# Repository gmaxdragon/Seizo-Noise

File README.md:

# Seizo-Noise

> **Engineering update, 24 October 2026:** A separate [**Seizo Noise v2.1 native KiCad source**](v2_1/ENGINEERING_REVIEW.md) and matching [BOM](purchasing/BOM_HalfLife_v2_1.csv) have been added. The narrative and screenshots below document the original **v1 ESP32/12V board**, not the simplified v2.1 5V Pi audio carrier. The root BOM now shows the **v2.1 priced subset** ($34.46 before missing shipping, tax and hardware); the complete legacy v1 BOM is [archived](purchasing/legacy_v1_BOM_archive.csv). v2.1 CAD has archived clean ERC/DRC but is not approved for PCB fabrication or order until the actual jack and potentiometer fit is checked. Neither board has been physically assembled or audio-tested. This note is a technical engineering update and does not alter the owner's account of the project.

## Current Seizo Noise v2.1 BOM and pricing (October 24, 2026)

**Estimated listed parts and PCB subtotal: $34.46 USD across 17 lines.** Includes a **provisional $4.00 PCB fabrication allowance**. This is **not** a final shipped/project cost. Shipping, sales tax, enclosure, standoffs, adapter/power-supply and other unpriced assembly items are **not included**. Prices come from saved catalog checks and are **not a live checkout quote**.

| Part | Quantity | Unit price (USD) | Line total (USD) |
| --- | ---: | ---: | ---: |
| [J1: 2-pin 5.08mm screw terminal](https://www.digikey.com/en/products/detail/on-shore-technology-inc/OSTTC022162/614558) | 1 | $0.58 | $0.58 |
| [F1: 0.75A hold resettable PTC fuse](https://www.digikey.com/en/products/detail/littelfuse-inc/RXEF075/5015922) | 1 | $0.56 | $0.56 |
| [D1: Schottky 1A 40V axial diode DO41](https://www.digikey.com/en/products/detail/panjit-international-inc/1N5819-R2-00001/15806519) | 1 | $0.28 | $0.28 |
| [C1: 470uF 25V low ESR radial 10mm 5mm leads](https://www.digikey.com/en/products/detail/panasonic-electronic-components/EEU-FR1E471/2433553) | 1 | $1.06 | $1.06 |
| [C2: 100nF X7R 50V radial 5.08mm - KEMET C052C104K5R5TA](https://www.digikey.com/en/products/detail/kemet/C052C104K5R5TA/12699186) | 1 | $1.29 | $1.29 |
| [J4: 3.5mm TRS stereo right-angle PCB jack](https://www.digikey.com/en/products/detail/same-sky-formerly-cui-devices/SJ1-3533NG/738701) | 1 | $1.69 | $1.69 |
| [R1 R2: 4.7k 1/4W THT resistor](https://www.digikey.com/en/products/detail/yageo/CFR-25JB-52-4K7/1846) | 2 | $0.10 | $0.20 |
| [R3: 100k 1/4W THT resistor](https://www.digikey.com/en/products/detail/yageo/CFR-25JB-52-100K/245) | 1 | $0.11 | $0.11 |
| [RV1: 10k logarithmic 20mm D-shaft THT potentiometer](https://www.digikey.com/en/products/detail/bourns-inc/PTV09A-2020F-A103/3781098) | 1 | $1.23 | $1.23 |
| [J3: 40-pin breakaway 2.54mm THT header](https://www.digikey.com/en/products/detail/PRPC040SAAN-RC/S1011EC-40-ND/2775214) | 1 | $1.23 | $1.23 |
| [EXT AMP: Assembled PAM8302 mono class-D amplifier](https://www.digikey.com/en/products/detail/adafruit-industries-llc/2130/5761279) | 1 | $3.95 | $3.95 |
| [EXT SPK: Enclosed 4ohm 3W speaker with JST-PH lead](https://www.digikey.com/en/products/detail/adafruit-industries-llc/3351/6612456) | 1 | $3.95 | $3.95 |
| [EXT MIC: USB microphone for Raspberry Pi](https://www.digikey.com/en/products/detail/adafruit-industries-llc/3367/6623861) | 1 | $5.95 | $5.95 |
| [EXT WIRE: 22AWG stranded silicone ribbon wire 10x 1m](https://www.digikey.com/en/products/filter/flat-ribbon-cables/adafruit-industries-llc/472) | 1 | $4.25 | $4.25 |
| [EXT AUX: 3.5mm TRS stereo male-to-male 1m cable](https://www.digikey.com/en/products/detail/adafruit-industries-llc/4066/9838303) | 1 | $2.95 | $2.95 |
| [EXT KNOB: 6mm D-shaft potentiometer knob](https://www.digikey.com/en/products/detail/cliff-electronic-components-ltd/CL170823BR/25579849) | 1 | $1.18 | $1.18 |
| [Custom 85x60mm 2-layer PCB (ESTIMATE ONLY; verify manufacturer quote)](https://jlcpcb.com/) | 1 | $4.00 | $4.00 |
| **TOTAL (priced items only)** | | | **$34.46** |

**Import troubleshooting:** [BOM.csv](BOM.csv) now has explicit numeric `Unit Price`, `Price` and `Total Cost` fields. An earlier CSV format still caused Half-Life to show **no price** for all 17 items, so the account-side import is **not verified**; re-import from the repo and inspect the Unit column. [Recovery notes](purchasing/HALFLIFE_PRICE_IMPORT_RECOVERY.md). The same current revision is backed up in [purchasing/BOM_HalfLife_v2_1.csv](purchasing/BOM_HalfLife_v2_1.csv). [All unpriced engineering items](purchasing/BOM_Engineering_v2_1.csv) are tracked separately and are not assumed free. Importing the BOM into Half-Life and seeing the prices there is still a separate verification step.

**Version warning:** This is the **v2.1 5V Raspberry Pi analog-audio board**, not the original v1 ESP32/12V design. The original v1 prices further down this README are historical and do not apply to the current BOM.

## What I made

Seizo Noise is a PCB I designed for my robotic arm. The main reason I made it was that I wanted the arm to be able to talk and take in voice commands. I thought it would be really cool to say, “Hey, Seizo,” and have it respond with something like, “Yeah, what’s up?” I also want it to be able to play music.

It’s a big PCB with USB-C and connections for a separate microphone module and amplifier module. It also has more connectors for sensors and other parts of my robotic arm. The goal is to bring these connections together and make the whole setup simpler.

## What it does

The board is designed to receive audio from my Raspberry Pi or laptop through the headphone output, using an AUX cable plugged directly into the PCB. It has a switch to choose the audio source and a knob to adjust the volume.

It also connects to a microphone module, an amplifier module, and additional sensors. The amplifier connects to the speaker. Eventually, I want the microphone and software to let me talk to the robotic arm and have it respond. That voice interaction is still something I need to make work and test.

## Why I made it

I made it because constantly running motor commands and being on my phone to train the arm has gotten really annoying. I wanted to simplify that so I could eventually give it instructions by talking instead.

I also wanted one board to bring the audio and sensor connections together instead of having everything spread out. Making the robot easier to use is the main reason, but having it talk back would also be way cooler, in my opinion.

The AUX input also means it isn’t only for the arm. I want to connect my laptop and use the speaker setup for that too.

## My work and what I learned

I worked on the schematic, added components and connections, arranged the PCB, and routed it. I worked through a ton of errors, especially when ERC and DRC kept failing. That got really annoying at some points, but figuring out what the errors meant helped me learn.

Week 1 was mostly about messing around and learning how KiCad works. This project was more about understanding specific design rules, footprints, trace widths, and filling areas of the PCB with ground copper.

I learned that getting the schematic connected is only part of the work. I also had to think about where the components go, whether the footprints match, and whether the routing follows the rules. Working through those problems made me understand the whole process much better.

## Parts and current progress

I haven’t personally checked many of the individual parts yet. The connections I’m most familiar with are the headphone outputs on my laptop and Raspberry Pi. I chose an AUX input because those are simple to reuse, and it lets the board work with either device instead of being only for the robotic arm.

The schematic and routing work are finished in KiCad. I still need to finish checking the parts and purchasing choices, get the PCB made, solder it, and test the actual hardware. Nothing has been manufactured or assembled yet, so I haven’t tested the finished board playing audio or recording through the microphone.

## Help and sources

I used tutorials, datasheets, and KiCad’s tools throughout the project. I also talked to friends at school for help understanding things like different modules, voltage requirements, capacitor selection, and how to make the design safer.

ERC and DRC were especially helpful because they pointed out errors that I would have struggled to find myself. I used them a ton while working through the schematic and routing.

I also used AI to help plan the project, research components, explain errors, and give me instructions. ChatGPT directly edited project files too, including changes to the layout, routing, footprints, and labels when I got stuck. I did hands-on schematic and routing work myself, but the final files also include those AI-made changes.

## Project screenshots

These are CAD screenshots, not photographs of assembled hardware. They show the original Seizo Audio v1.0 carrier. The lower-cost purchase option below uses a wired regulator rather than the pictured Pololu module.

## Design files

| File | Link |
| --- | --- |
| KiCad schematic | [speakerpcb.kicad_sch](hardware/speakerpcb.kicad_sch) |
| PCB layout | [speakerpcb.kicad_pcb](hardware/speakerpcb.kicad_pcb) |
| Complete KiCad project | [speakerpcb.kicad_pro](hardware/speakerpcb.kicad_pro) |
| Board rules | [speakerpcb.kicad_dru](hardware/speakerpcb.kicad_dru) |
| Included footprints | [Seizo_Audio.pretty](hardware/Seizo_Audio.pretty) |
| Included symbols | [Seizo_Audio.kicad_sym](hardware/Seizo_Audio.kicad_sym) |
| Original assembly instructions | [Assembly.md](docs/Assembly.md) |
| Original connector pin maps | [Connections.md](docs/Connections.md) |
| Lower-cost assembly option | [Low_cost_assembly.md](docs/Low_cost_assembly.md) |
| Native schematic check | [ERC.rpt](validation/ERC.rpt) |
| Native board and schematic-parity check | [DRC.rpt](validation/DRC.rpt) |
| Gerbers and drills | [Seizo_Audio_Gerbers.zip](fabrication/Seizo_Audio_Gerbers.zip) |

Open `hardware/speakerpcb.kicad_pro` with its bundled libraries. The existing ERC/DRC reports apply to the published carrier CAD. No PCB copper or schematic nets were changed in this purchasing update, and those reports do not validate the new wired regulator assembly or physical operation.

## Legacy v1 hardware and purchase scope (archived)

**The $3.95 Adafruit 4711 regulator is NOT a drop-in replacement for the original Pololu footprint.** Leave the Pololu and its socket uninstalled. Use three short insulated wires: carrier U2 pad 3 to Vin, pad 4 to GND, and pad 5 to 3V on Adafruit 4711. Follow the [assembly option](docs/Low_cost_assembly.md) before assembling or powering. Never connect this regulator to 12V.

| Item | Current selection |
| --- | --- |
| Carrier PCB | Existing 100 x 80mm, two-layer Seizo Audio v1.0 |
| Controller | Exact bare ESP32-S3-WROOM-1-N8R8, sourced separately from Mouser |
| 3.3V supply | Adafruit 4711 breakout wired to existing U2 pads; original CAD model remains Pololu |
| Main power terminals | On Shore OSTTC022162, 5.08mm pitch, two pieces |
| Playback | Pi/laptop AUX output, source selector and volume control |
| Microphone | Adafruit 3421 SPH0645LM4H, wired to J9 by signal |
| Amplifier | ShillehTek TPA3118 mono module |
| Speaker | One NEW Visaton FR 10 F - 4 OHM, 20W rated |
| Amplifier supply | Tri-Mag L6R30-120, 12V 2.5A, plus barrel adapter |
| Deferred equipment | PCM5102 DAC and additional sensors, as in the previous initial-build plan |
| Physical status | Not assembled, powered or audio-tested |

## Legacy v1 bill of materials (archived)

**Estimated selected-parts subtotal: $68.38.** This includes the new speaker, required ESP32, short-wiring pack and barrel adapter. The 30-line DigiKey portion is $55.11. The ESP32 is $6.28 from Mouser and the amplifier is $6.99 from ShillehTek.

The owner's separate $4 PCB allowance brings this to $72.38 before tax, delivery, tariffs and remaining accessories. AUX/USB cables, enclosure, mounting and insulation costs are not included or assumed free. The owner's roughly $20 tax/shipping allowance is not a checkout quote. See [Budget.md](purchasing/Budget.md).

New and major component listings were reviewed on October 22, 2026. Mouser listed the exact ESP32-S3-WROOM-1-N8R8 in stock at $6.28 on October 22, 2026; confirm final stock, shipping and tariffs at checkout. Other small-part prices are retained from earlier catalog checks. The user's reported $83 cart has not been inspected; this is not a claim to have corrected that live cart.

| References | Qty | Item / exact part | Unit USD | Line USD | Supplier |
| --- | ---: | --- | ---: | ---: | --- |
| External speaker | 1 | 4-ohm loudspeaker - Visaton FR 10 F - 20W (FR 10 F - 4 OHM) | 11.71 | 11.71 | [DigiKey](https://www.digikey.com/en/products/detail/visaton-gmbh-co-kg/FR-10-F-4-OHM/10650582) |
| U1 | 1 | ESP32-S3-WROOM-1-N8R8 bare module (ESP32-S3-WROOM-1-N8R8) | 6.28 | 6.28 | [Mouser](https://www.mouser.com/en/ProductDetail/Espressif-Systems/ESP32-S3-WROOM-1-N8R8) |
| U2 | 1 | 3.3V regulator breakout - wired assembly (4711) | 3.95 | 3.95 | [DigiKey](https://www.digikey.com/en/products/detail/adafruit-industries-llc/4711/13162412) |
| U3 | 1 | USB data ESD protector (USBLC6-2SC6) | 0.54 | 0.54 | [DigiKey](https://www.digikey.com/en/products/detail/stmicroelectronics/USBLC6-2SC6/1040559) |
| J1 | 1 | USB-C receptacle (USB4085-GF-A) | 0.91 | 0.91 | [DigiKey](https://www.digikey.com/en/products/detail/gct/USB4085-GF-A/9859733) |
| J8 | 1 | Stereo AUX input jack (SJ1-3533NG) | 1.69 | 1.69 | [DigiKey](https://www.digikey.com/en/products/detail/same-sky-formerly-cui-devices/SJ1-3533NG/738701) |
| J3 J4 | 2 | Two-position power terminal block (OSTTC022162) | 0.58 | 1.16 | [DigiKey](https://www.digikey.com/en/products/detail/on-shore-technology-inc/OSTTC022162/614558) |
| F1 | 1 | USB resettable fuse (1206L050/15YR) | 0.68 | 0.68 | [DigiKey](https://www.digikey.com/en/products/detail/littelfuse-inc/1206L050-15YR/2486168) |
| F2 | 1 | MINI blade fuse holder (3568) | 1.31 | 1.31 | [DigiKey](https://www.digikey.com/en/products/detail/keystone-electronics/3568/2137306) |
| F2 insert | 1 | 2A MINI blade fuse (0297002.WXNV) | 0.39 | 0.39 | [DigiKey](https://www.digikey.com/en/products/detail/littelfuse-inc/0297002-WXNV/124900) |
| D1 | 1 | Reverse-polarity diode (1N5822) | 0.71 | 0.71 | [DigiKey](https://www.digikey.com/en/products/detail/taiwan-semiconductor-corporation/1N5822/7366597) |
| RV1 | 1 | Volume potentiometer (PTV09A-2020F-A103) | 1.23 | 1.23 | [DigiKey](https://www.digikey.com/en/products/detail/bourns-inc/PTV09A-2020F-A103/3781098) |
| SW3 | 1 | Audio source selector (OS102011MS2QN1) | 0.80 | 0.80 | [DigiKey](https://www.digikey.com/en/products/detail/c-k/OS102011MS2QN1/411602) |
| SW1 SW2 | 2 | RESET and BOOT buttons (B3F-1000) | 0.35 | 0.70 | [DigiKey](https://www.digikey.com/en/products/detail/aratas-america-llc/B3F-1000/33150) |
| C1 C5 | 2 | 10uF ceramic capacitor (CL31A106KAHNFNE) | 0.25 | 0.50 | [DigiKey](https://www.digikey.com/en/products/detail/samsung-electro-mechanics/CL31A106KAHNFNE/3888696) |
| C2 C7 C9 C10 | 4 | 100nF ceramic capacitor (CL31B104KBCNNNC) | 0.14 | 0.56 | [DigiKey](https://www.digikey.com/en/products/detail/samsung-electro-mechanics/CL31B104KBCNNNC/3886675) |
| C3 C4 | 2 | 1uF ceramic capacitor (CL31B105KBHSNNE) | 0.24 | 0.48 | [DigiKey](https://www.digikey.com/en/products/detail/samsung-electro-mechanics/CL31B105KBHSNNE/3891179) |
| C6 | 1 | 470uF electrolytic capacitor (EEU-FR1E471) | 1.06 | 1.06 | [DigiKey](https://www.digikey.com/en/products/detail/panasonic-industry/EEU-FR1E471/2433553) |
| C8 | 1 | 2.2uF audio coupling capacitor (CL31B225KAHNNNE) | 0.21 | 0.21 | [DigiKey](https://www.digikey.com/en/products/detail/samsung-electro-mechanics/CL31B225KAHNNNE/3886730) |
| R1 R2 R13 R17 | 4 | 10k resistor (RC1206FR-0710KL) | 0.11 | 0.44 | [DigiKey](https://www.digikey.com/en/products/detail/yageo/RC1206FR-0710KL/731430) |
| R3 R4 | 2 | 5.1k resistor (RC1206FR-075K1L) | 0.10 | 0.20 | [DigiKey](https://www.digikey.com/en/products/detail/yageo/RC1206FR-075K1L/728947) |
| R5 R6 | 2 | 22 ohm resistor (RC1206FR-0722RL) | 0.11 | 0.22 | [DigiKey](https://www.digikey.com/en/products/detail/yageo/RC1206FR-0722RL/728687) |
| R9 R10 R11 R12 R18 R19 | 6 | 4.7k resistor (RC1206FR-074K7L) | 0.10 | 0.60 | [DigiKey](https://www.digikey.com/en/products/detail/yageo/RC1206FR-074K7L/728887) |
| R14 | 1 | 18k resistor (RC1206FR-0718KL) | 0.10 | 0.10 | [DigiKey](https://www.digikey.com/en/products/detail/yageo/RC1206FR-0718KL/731539) |
| R15 | 1 | 100k resistor (RC1206FR-07100KL) | 0.10 | 0.10 | [DigiKey](https://www.digikey.com/en/products/detail/yageo/RC1206FR-07100KL/728492) |
| R16 | 1 | 6.8k resistor (RC1206FR-076K8L) | 0.10 | 0.10 | [DigiKey](https://www.digikey.com/en/products/detail/yageo/RC1206FR-076K8L/729028) |
| J5 J6 J7 J9 J10 J11 J12 | 1 | 40-pin breakaway header strip (PRPC040SAAN-RC) | 1.23 | 1.23 | [DigiKey](https://www.digikey.com/en/products/detail/sullins-connector-solutions/PRPC040SAAN-RC/2775214) |
| External J9 | 1 | I2S microphone breakout (3421) | 6.95 | 6.95 | [DigiKey](https://www.digikey.com/en/products/detail/adafruit-industries-llc/3421/6691114) |
| External J4 J5 | 1 | Mono amplifier module (ST-HLHQRTMBQEIH) | 6.99 | 6.99 | [ShillehTek](https://shillehtek.com/products/tpa3118-pbtl-single-digital-amplifier-board-1x60w) |
| External supply | 1 | 12V amplifier power supply (L6R30-120) | 10.33 | 10.33 | [DigiKey](https://www.digikey.com/en/products/detail/tri-mag-llc/L6R30-120/7682642) |
| REGULATOR_AND_SHORT_POWER_WIRING | 1 | 22 AWG insulated wire - 1m ten-conductor ribbon (6180) | 4.25 | 4.25 | [DigiKey](https://www.digikey.com/en/products/detail/adafruit-industries-llc/6180/26690472) |
| 12V_ADAPTER | 1 | Female 2.1mm DC barrel to screw-terminal adapter (368) | 2.00 | 2.00 | [DigiKey](https://www.digikey.com/en/products/detail/adafruit-industries-llc/368/5629434) |

| **Selected-parts subtotal** | | | | **68.38** | |

## Import files

[Half-Life BOM](BOM.csv) and [durable component list](purchasing/Selected_components.csv) contain the same 32 priced rows with purposes. [DigiKey CSV](purchasing/Seizo_Noise_DigiKey.csv) has 30 rows, with the speaker first and no ESP32. [Other suppliers](purchasing/Other_suppliers.csv) lists the ESP32 and amplifier separately.

The speaker's exact DigiKey SKU is **2056-FR10F-4OHM-ND**. Its cart reference is `SPEAKER_4OHM_20W`. An amplifier module is not the loudspeaker. The previous file already included the speaker SKU; the reason it was missing from the user's cart was not established.

Use an empty project cart or remove obsolete/duplicate lines before importing. Reimporting does not establish that existing cart items were removed. Verify 30 DigiKey rows, including one speaker, before checkout. In Half-Life verify 32 parts and the prices before saving; a platform sync can overwrite root `BOM.csv`. No live cart or authenticated Half-Life import was run by this update.

## Sources and records

- [Original development journal](JOURNAL.md), synced by Half-Life. Entries and hours were not changed.
- [Current component selection](purchasing/Selected_components.csv), [budget](purchasing/Budget.md), and [status](purchasing/BOM_status.json).
- [Earlier engineering requirements](purchasing/BOM_engineering.csv) and [previous selection](purchasing/Selected_components_previous.csv) are historical records, not current shopping lists.
- [Adafruit regulator](https://www.adafruit.com/product/4711), [terminal manufacturer drawing](https://www.on-shore.com/wp-content/uploads/OSTTCXX2162.pdf), and supplier links in the BOM support the new selections.
- [CAD import provenance](docs/import_provenance.json) and existing native checks under `validation/`.
- AI assistance was used for parts research, CSV formatting and technical assembly notes. The six owner-approved narrative sections above remain unchanged. No unaided research or physical testing is claimed.

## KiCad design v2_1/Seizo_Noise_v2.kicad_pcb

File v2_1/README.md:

# Seizo Noise v2.1 — CHECKED CAD / HOLD FOR PHYSICAL RELEASE

This project is the **new, simpler 5V analog speaker/interface board** for Seizo. It is **not** the old ESP32/12V board.

## BOM price (listed parts only)

**$34.46 USD estimated subtotal, 17 lines, including a provisional $4.00 bare PCB allowance.** Shipping, tax, enclosure, mount hardware, actual 5V power-adapter requirements and missing supplies are **not yet priced**. This is not an order-ready/landed total. Open [numeric BOM](../BOM.csv) or [full price table](../purchasing/PRICED_BOM_SUMMARY.md).

## Open in KiCad

1. Extract the complete ZIP into one folder (do not pull out just the PCB file).
2. Open `Seizo_Noise_v2.kicad_pro` in **KiCad 10**.
3. Open the schematic and PCB through the project manager, preserving `Seizo_V2_Symbols.kicad_sym`, `Seizo_Noise_v2.pretty`, the local library tables, and `models/`.
4. To rerun checks, use Inspect -> Electrical Rules Checker in the schematic and Inspect -> Design Rules Checker in the PCB, with **Refill zones** and **Test for schematic parity** enabled.

**Revision v2.1 moves the AUX jack closer to the board edge, shifts the volume shaft farther toward the right edge, corrects a discovered 10.0mm-vs-8.2mm potentiometer mounting-tab footprint mismatch, and enlarges the jack insertion slots; see `docs/research/ENGINEERING_RELEASE_AUDIT.md`.**

The project was created from the user-uploaded `sz2(1).kicad_sch` and intentionally discarded its empty `.kicad_pcb` placeholder. The upload used `5V_AUDIO` and `+5V_AUDIO` for different nets, leaving the amp connector without the intended protected supply; v2 merges them into the single `+5V_AUDIO` rail.

## What it does

- Audio from a Raspberry Pi or laptop goes to J4 (Same Sky SJ1-3533NG, 3.5mm stereo AUX).
- R1/R2 (4.7k each) isolate and combine left and right to mono.
- RV1 (Bourns PTV09A-2020F-A103) controls analog volume, and R3 (100k) pulls the amp input to ground.
- External protected **regulated 5V only** enters J1. F1 is a 0.75A-hold PTC, D1 is a 1N5819 Schottky (PIN1/cathode on the downstream +5V rail), and C1/C2 stabilize the rail.
- J3 connects by four labelled wires to the **separately purchased Adafruit PAM8302 (product 2130)**: pin1 VIN, pin2 GND, pin3 A+, pin4 A−/GND.
- The **speaker attaches directly to PAM8302 SPK+/SPK−**; do not run speaker output to J3 or board GND.
- The USB microphone connects **directly to the Pi**, not to this board. The Pi performs speech recognition and Seizo's supervised action-validation process.

## Native verification evidence

On KiCad CLI 10.0.7, first in the original local build and then **again in a clean copied project directory**:

- ERC: **0 errors, 0 warnings**.
- DRC: **0 violations, 0 unconnected pads, 0 footprint errors** with ground refill and schematic-to-PCB parity.
- Independent pad/net comparison: **29 assigned electrical pad connections, no mismatches**.
- Board: **85 x 60 mm; 2 copper layers; nominal 1.6mm; 4 x M3 NPTH holes; 14 electrical footprints; 4 mounting footprints**.
- Routing: routed copper traces on B.Cu with a F.Cu GND pour; independent audited segment count is in `validation/INDEPENDENT_RELEASE_AUDIT.json`.
- Drill preview: 31 plated holes (including three routed 2.2×1.1mm AUX plated slots and two oversized 3.3mm plated potentiometer mounting holes); 4 unplated 3.2mm M3 mounting holes; PTH/NPTH drills separate.

Updated reports are under `validation/`; the final v2.1 3D preview is `docs/plots/Seizo_Noise_v2_1_CAD_RENDER.png`. **This is digital CAD validation only, not a physical or electrical functional demonstration.** Existing KiCad ignored-check categories are disclosed in the reports; no new DRC exemption was added to hide copper/clearance faults.

## Ordering status — HOLD

The `fabrication/GERBERS_DRAFT_DO_NOT_ORDER` folder is a complete native Gerber/drill **preview**. **Do not send it to fabrication yet**, even though KiCad checks pass. Exact procurement and mechanical-fit review must precede release; see `docs/TOMORROW_HANDOFF.md` and `docs/ASSEMBLY_AND_TEST.md`.

Purchasing lists from v1 are **not valid for this new board**. The user reports owning a 5V 1A adapter but its loaded voltage, connector fit and polarity have not been independently measured; remaining components and their physical fit are unverified. The 65-dollar Hack Club project target has not been reconciled as a delivered purchase quote.

## Links to primary hardware documentation

- [Same Sky SJ1-3533NG jack datasheet](https://www.sameskydevices.com/product/resource/sj1-353xng.pdf)
- [Bourns PTV09A dimensions](https://www.bourns.com/docs/product-datasheets/PTV09.pdf)
- [Littelfuse RXEF075 PTC datasheet](https://www.littelfuse.com/assetdocs/littelfuse_ptc_radial_leaded_rxef_datasheet?assetguid=e9a7b6b3-79ce-478c-a39a-0a70ee48ccec)
- [Adafruit PAM8302 product 2130 pinouts](https://learn.adafruit.com/adafruit-pam8302-mono-2-5w-class-d-audio-amplifier/pinouts)

AI assistance was used in this CAD revision for net correction, footprint generation, placement, routing, native checks, and documentation. This does not replace the author's KiCad work and does not claim assembled-hardware testing.

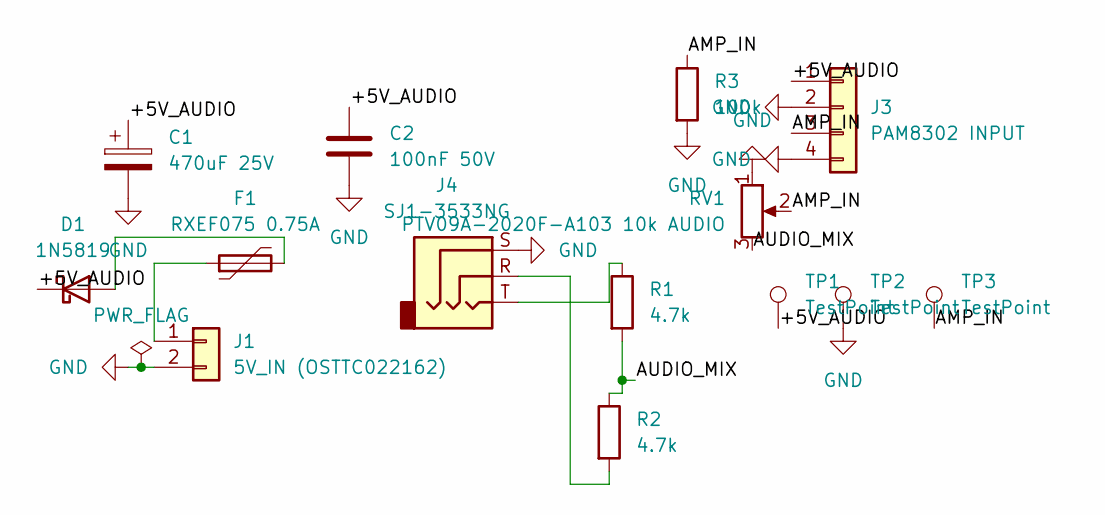
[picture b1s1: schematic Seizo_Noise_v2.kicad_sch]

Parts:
C1: 470uF 25V; C_Panasonic_EEUFR1E471_P5mm
C2: 100nF 50V; C_100nF_Radial_P5.08mm
D1: 1N5819; D_1N5819_DO41_P10.16mm
F1: RXEF075 0.75A; PTC_Littelfuse_RXEF075_P5.10mm
J1: 5V_IN (OSTTC022162); TerminalBlock_OSTTC022162_P5.08mm
J3: PAM8302 INPUT; PinHeader_1x04_P2.54mm_Vertical
J4: SJ1-3533NG; Jack_SJ1-3533NG
R1, R2: 4.7k; R_0207_P7.62mm
R3: 100k; R_0207_P7.62mm
RV1: PTV09A-2020F-A103 10k AUDIO; Pot_Bourns_PTV09A_2020F_A103
TP1, TP2, TP3: TestPoint; TP_THT_Probe_2.6mm

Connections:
/+5V_AUDIO: C1.1, C2.1, D1.1 (K), J3.1, TP1.1
/AMP_IN: J3.3, R3.1, RV1.2, TP3.1
/AUDIO_MIX: R1.2, R2.1, RV1.3
GND: C1.2, C2.2, J1.2, J3.2, J3.4, J4.S, R3.2, RV1.1, TP2.1
unnamed: D1.2 (A), F1.2
unnamed: F1.1, J1.1
unnamed: J4.R, R2.2
unnamed: J4.T, R1.1

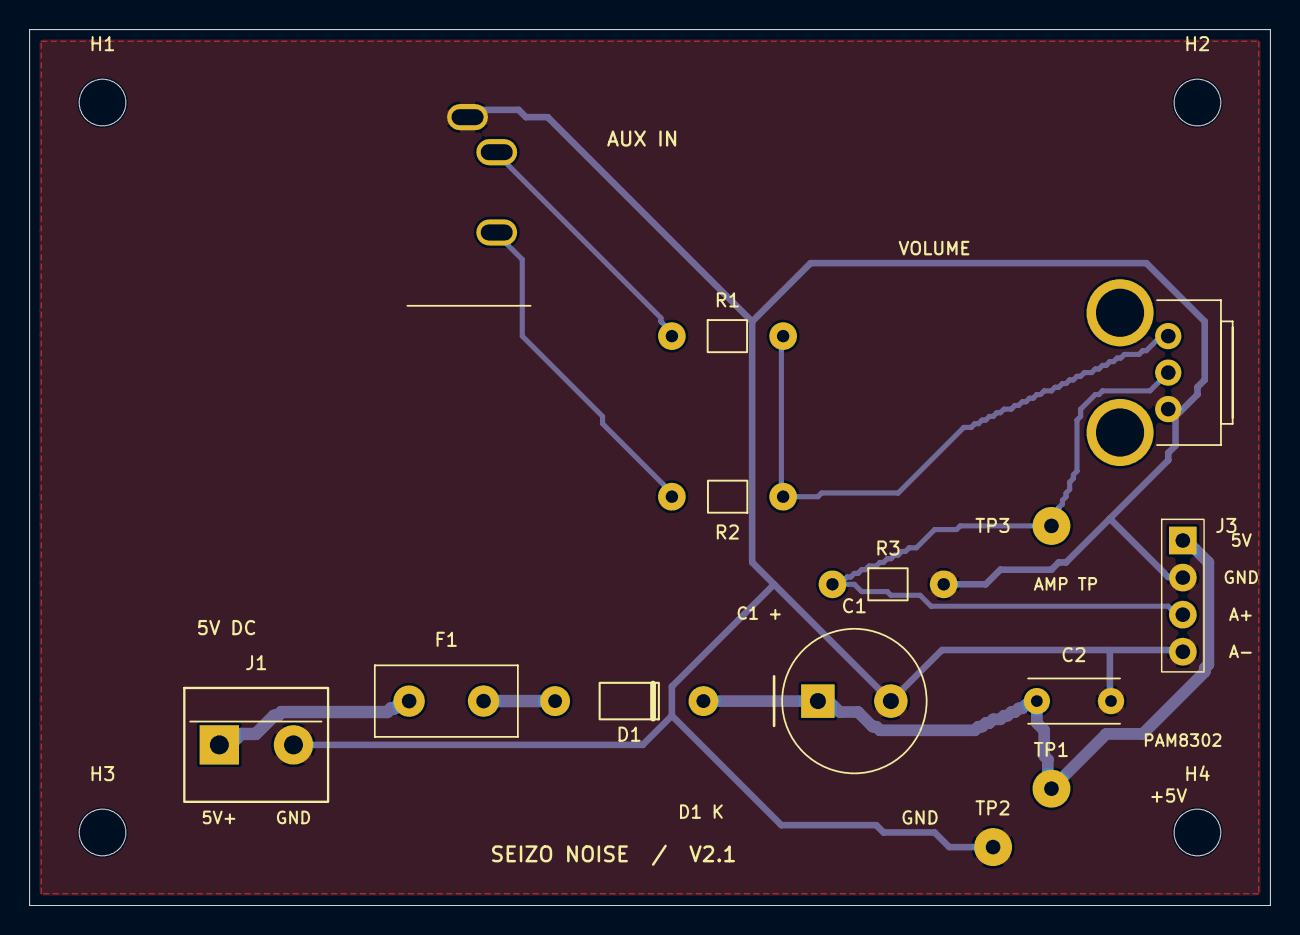
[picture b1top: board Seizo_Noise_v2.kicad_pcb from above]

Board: 2 copper layers, 85.0 x 60.0 mm, 18 parts (0 on the bottom side), 8 nets.

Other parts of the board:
H1, H2, H3, H4: M3 NPTH; MountingHole_M3_NPTH

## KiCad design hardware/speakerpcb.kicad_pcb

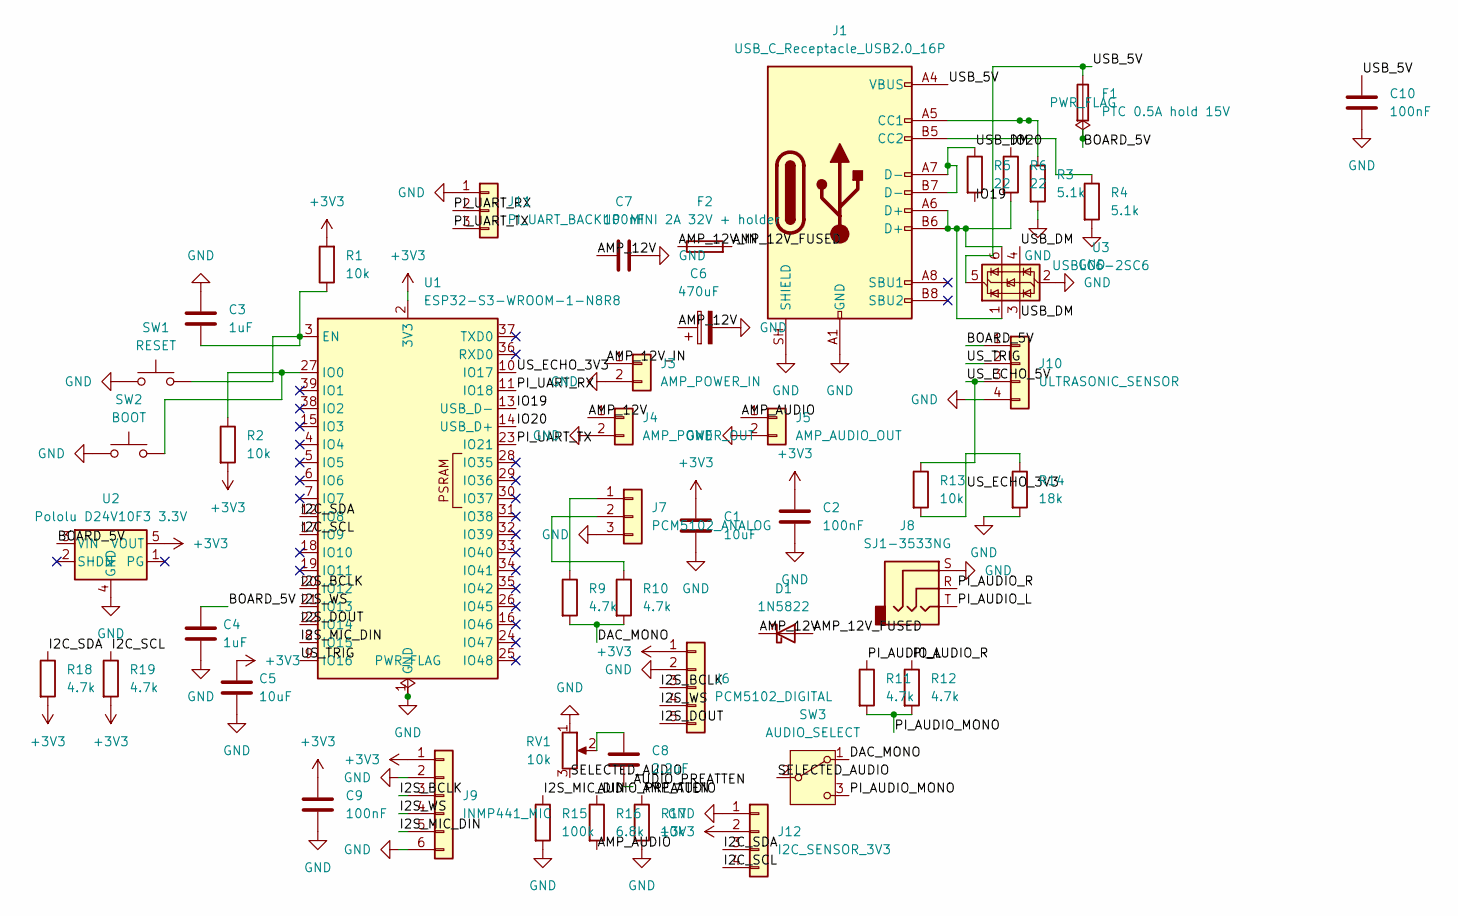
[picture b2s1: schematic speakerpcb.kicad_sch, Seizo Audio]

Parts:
C1: 10uF; C1_C_1206_3216Metric_Pad1_33x1_80mm_HandSolder; Rating 1206 ceramic X7R or X5R; 16V minimum; c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
C2: 100nF; C2_C_1206_3216Metric_Pad1_33x1_80mm_HandSolder; Rating 1206 ceramic X7R; 50V; 100nF
C3: 1uF; C3_C_1206_3216Metric_Pad1_33x1_80mm_HandSolder; Rating 1206 ceramic X7R or X5R; 16V minimum; c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
C4: 1uF; C4_C_1206_3216Metric_Pad1_33x1_80mm_HandSolder; Rating 1206 ceramic X7R or X5R; 16V minimum; c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
C5: 10uF; C5_C_1206_3216Metric_Pad1_33x1_80mm_HandSolder; Rating 1206 ceramic X7R or X5R; 16V minimum; c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
C6: 470uF; C6_CP_Radial_D10_0mm_P5_00mm; Rating 470uF 25V polarized; D10mm, pitch5mm; MPN EEUFR1E471
C7: 100nF; C7_C_1206_3216Metric_Pad1_33x1_80mm_HandSolder; Rating 1206 ceramic X7R; 50V; 100nF
C8: 2.2uF; C8_C_1206_3216Metric_Pad1_33x1_80mm_HandSolder; Rating 1206 ceramic X7R; 25V minimum; NONPOLAR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
C9: 100nF; C9_C_1206_3216Metric_Pad1_33x1_80mm_HandSolder; Rating 1206 ceramic X7R; 50V; 100nF
C10: 100nF; C10_C_1206_3216Metric_Pad1_33x1_80mm_HandSolder; Rating 1206 ceramic X7R; 50V; 100nF
D1: 1N5822; D1_D_DO_201AD_P15_24mm_Horizontal
F1: PTC 0.5A hold 15V; F1_Fuse_1206_3216Metric_Pad1_42x1_75mm_HandSolder; MPN 1206L050/15YR
F2: MINI 2A 32V + holder; F2_Fuseholder_Blade_Mini_Keystone_3568; MPN 3568 (PCB holder); 0297002.WXNV (insert)
J1: USB_C_Receptacle_USB2.0_16P; J1_USB_C_Receptacle_GCT_USB4085
J3: AMP_POWER_IN; J3_TerminalBlock_Phoenix_MKDS_1_5_2_5_08_1x02_P5_08mm_Horiz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; MPN 1715721
J4: AMP_POWER_OUT; J4_TerminalBlock_Phoenix_MKDS_1_5_2_5_08_1x02_P5_08mm_Horiz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; MPN 1715721
J5: AMP_AUDIO_OUT; J5_PinHeader_1x02_P2_54mm_Vertical
J6: PCM5102_DIGITAL; J6_PinHeader_1x05_P2_54mm_Vertical
J7: PCM5102_ANALOG; J7_PinHeader_1x03_P2_54mm_Vertical
J8: SJ1-3533NG; J8_Jack_3_5mm_CUI_SJ1_3533NG_Horizontal
J9: INMP441_MIC; J9_PinHeader_1x06_P2_54mm_Vertical
J10: ULTRASONIC_SENSOR; J10_PinHeader_1x04_P2_54mm_Vertical
J11: PI_UART_BACKUP; J11_PinHeader_1x03_P2_54mm_Vertical
J12: I2C_SENSOR_3V3; J12_PinHeader_1x04_P2_54mm_Vertical
R1: 10k; R1_R_1206_3216Metric_Pad1_30x1_75mm_HandSolder; Rating 1206 / 3216 metric; 1%; 0.25W minimum
R2: 10k; R2_R_1206_3216Metric_Pad1_30x1_75mm_HandSolder; Rating 1206 / 3216 metric; 1%; 0.25W minimum
R3: 5.1k; R3_R_1206_3216Metric_Pad1_30x1_75mm_HandSolder; Rating 1206 / 3216 metric; 1%; 0.25W minimum
R4: 5.1k; R4_R_1206_3216Metric_Pad1_30x1_75mm_HandSolder; Rating 1206 / 3216 metric; 1%; 0.25W minimum
R5: 22; R5_R_1206_3216Metric_Pad1_30x1_75mm_HandSolder; Rating 1206 / 3216 metric; 1%; 0.25W minimum
R6: 22; R6_R_1206_3216Metric_Pad1_30x1_75mm_HandSolder; Rating 1206 / 3216 metric; 1%; 0.25W minimum
R9: 4.7k; R9_R_1206_3216Metric_Pad1_30x1_75mm_HandSolder; Rating 1206 / 3216 metric; 1%; 0.25W minimum
R10: 4.7k; R10_R_1206_3216Metric_Pad1_30x1_75mm_HandSolder; Rating 1206 / 3216 metric; 1%; 0.25W minimum
R11: 4.7k; R11_R_1206_3216Metric_Pad1_30x1_75mm_HandSolder; Rating 1206 / 3216 metric; 1%; 0.25W minimum
R12: 4.7k; R12_R_1206_3216Metric_Pad1_30x1_75mm_HandSolder; Rating 1206 / 3216 metric; 1%; 0.25W minimum
R13: 10k; R13_R_1206_3216Metric_Pad1_30x1_75mm_HandSolder; Rating 1206 / 3216 metric; 1%; 0.25W minimum
R14: 18k; R14_R_1206_3216Metric_Pad1_30x1_75mm_HandSolder; Rating 1206 / 3216 metric; 1%; 0.25W minimum
R15: 100k; R15_R_1206_3216Metric_Pad1_30x1_75mm_HandSolder; Rating 1206 / 3216 metric; 1%; 0.25W minimum
R16: 6.8k; R16_R_1206_3216Metric_Pad1_30x1_75mm_HandSolder; Rating 1206 / 3216 metric; 1%; 0.25W minimum
R17: 10k; R17_R_1206_3216Metric_Pad1_30x1_75mm_HandSolder; Rating 1206 / 3216 metric; 1%; 0.25W minimum
R18: 4.7k; R18_R_1206_3216Metric_Pad1_30x1_75mm_HandSolder; Rating 1206 / 3216 metric; 1%; 0.25W minimum
R19: 4.7k; R19_R_1206_3216Metric_Pad1_30x1_75mm_HandSolder; Rating 1206 / 3216 metric; 1%; 0.25W minimum
RV1: 10k; RV1_Potentiometer_Bourns_PTV09A_2_Single_Horizontal; MPN PTV09A-2020F-A103
SW1: RESET; SW1_SW_PUSH_6mm
SW2: BOOT; SW2_SW_PUSH_6mm
SW3: AUDIO_SELECT; SW3_SW_Slide_SPDT_Straight_CK_OS102011MS2Q; MPN OS102011MS2QN1
U1: ESP32-S3-WROOM-1-N8R8; U1_ESP32_S3_WROOM_1_GroundDrill_030
U2: Pololu D24V10F3 3.3V; U2_Pololu_D24V10F3_Socket; MPN Pololu 2830 D24V10F3
U3: USBLC6-2SC6; U3_SOT_23_6

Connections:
+3V3: C1.1, C2.1, C5.1, C9.1, J6.1, J9.1, J12.2, R1.2, R2.2, R18.2, R19.2, U1.2 (3V3), U2.5 (VOUT)
/AMP_12V: C6.1, C7.1, D1.1 (K), J4.1
/AMP_12V_FUSED: D1.2 (A), F2.2
/AMP_12V_IN: F2.1, J3.1
/AMP_AUDIO: J5.1, R16.2, R17.1
/AUDIO_PREATTEN: C8.2, R16.1
/BOARD_5V: C4.1, F1.2, J10.1, U2.3 (VIN)
/DAC_MONO: R9.2, R10.2, SW3.1 (A)
/I2C_SCL: J12.4, R19.1, U1.17 (IO9)
/I2C_SDA: J12.3, R18.1, U1.12 (IO8)
/I2S_BCLK: J6.3, J9.3, U1.20 (IO12)
/I2S_DOUT: J6.5, U1.22 (IO14)
/I2S_MIC_DIN: J9.5, R15.1, U1.8 (IO15)
/I2S_WS: J6.4, J9.4, U1.21 (IO13)
/IO19: R5.2, U1.13 (USB_D-)
/IO20: R6.1, U1.14 (USB_D+)
/PI_AUDIO_L: J8.T, R11.1
/PI_AUDIO_MONO: R11.2, R12.2, SW3.3 (C)
/PI_AUDIO_R: J8.R, R12.1
/PI_UART_RX: J11.2, U1.11 (IO18)
/PI_UART_TX: J11.3, U1.23 (IO21)
/SELECTED_AUDIO: RV1.3, SW3.2 (B)
/USB_5V: C10.1, F1.1, J1.A4 (VBUS), J1.A9 (VBUS), J1.B4 (VBUS), J1.B9 (VBUS), U3.5 (VBUS)
/USB_DM: J1.A7 (D-), J1.B7 (D-), R5.1, U3.3 (I/O2), U3.4 (I/O2)
/US_ECHO_3V3: R13.2, R14.1, U1.10 (IO17)
/US_ECHO_5V: J10.3, R13.1
/US_TRIG: J10.2, U1.9 (IO16)
GND: C1.2, C2.2, C3.1, C4.2, C5.2, C6.2, C7.2, C9.2, C10.2, J1.A1 (GND), J1.A12 (GND), J1.B1 (GND), J1.B12 (GND), J1.SH (SHIELD), J3.2, J4.2, J5.2, J6.2, J7.3, J8.S, J9.2, J9.6, J10.4, J11.1, J12.1, R3.2, R4.2, R14.2, R15.2, R17.2, RV1.1, SW1.1, SW2.1, U1.1 (GND), U1.40 (GND), U1.41 (GND), U2.4 (GND), U3.2 (GND)
unnamed: C8.1, RV1.2
unnamed: J1.A5 (CC1), R3.1
unnamed: J1.B5 (CC2), R4.1
unnamed: J1.A6 (D+), J1.B6 (D+), R6.2, U3.1 (I/O1), U3.6 (I/O1)
unnamed: J7.1, R9.1
unnamed: J7.2, R10.1
unnamed: C3.2, R1.1, SW1.2, U1.3 (EN)
unnamed: R2.1, SW2.2, U1.27 (IO0)

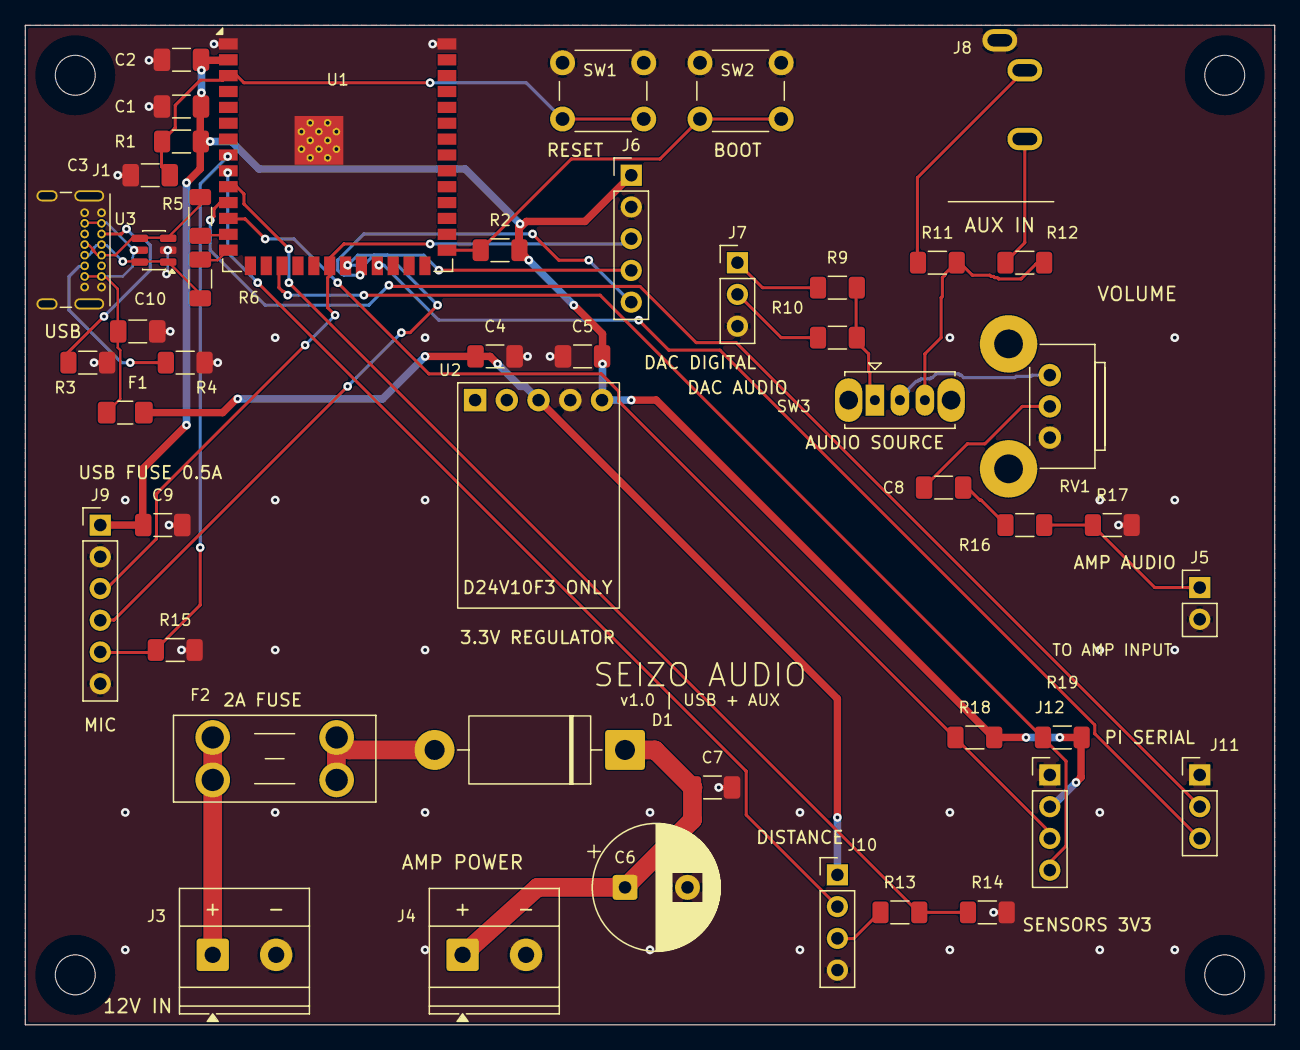
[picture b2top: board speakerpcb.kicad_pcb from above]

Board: 2 copper layers, 100.0 x 80.0 mm, 52 parts (0 on the bottom side), 36 nets.

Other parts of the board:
H1: M3 screw; H1_MountingHole_3_2mm_M3
H2: M3 screw; H2_MountingHole_3_2mm_M3
H3: M3 screw; H3_MountingHole_3_2mm_M3
H4: M3 screw; H4_MountingHole_3_2mm_M3

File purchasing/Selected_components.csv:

Item,Quantity,Unit Price,Vendor,URL,Purpose,Manufacturer Part Number,DigiKey Part Number,References,Line Total,Price Basis
4-ohm loudspeaker - Visaton FR 10 F - 20W,1,11.71,DigiKey,https://www.digikey.com/en/products/detail/visaton-gmbh-co-k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,One NEW speaker; connect directly to amplifier SPK+ and SPK-; not a microphone or amplifier module,FR 10 F - 4 OHM,2056-FR10F-4OHM-ND,External speaker,11.71,USD catalog listing reviewed 2026-10-22; exact DigiKey SKU verified
ESP32-S3-WROOM-1-N8R8 bare module,1,6.28,Mouser,https://www.mouser.com/en/ProductDetail/Espressif-Systems/ES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,Required exact N8R8 module; Mouser part 356-EP32S3WROOM1N8R8; excludes N8-only and 1U variants,ESP32-S3-WROOM-1-N8R8,,U1,6.28,Mouser listed $6.28 per module and in stock on 2026-10-22; verify shipping tariff and checkout before ordering
3.3V regulator breakout - wired assembly,1,3.95,DigiKey,https://www.digikey.com/en/products/detail/adafruit-industri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,Adafruit 4711; connect with three insulated wires to U2 pads 3/4/5; NOT a Pololu footprint drop-in; omit Pololu and socket,4711,1528-4711-ND,U2,3.95,USD catalog listing reviewed 2026-10-22; rated 3.4-5.5V input
USB data ESD protector,1,0.54,DigiKey,https://www.digikey.com/en/products/detail/stmicroelectronic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,Protects USB data lines from static discharge,USBLC6-2SC6,497-5235-1-ND,U3,0.54,Previous catalog check
USB-C receptacle,1,0.91,DigiKey,https://www.digikey.com/en/products/detail/gct/USB4085-GF-A/9859733,USB power and data input,USB4085-GF-A,2073-USB4085-GF-ACT-ND,J1,0.91,Previous catalog check
Stereo AUX input jack,1,1.69,DigiKey,https://www.digikey.com/en/products/detail/same-sky-formerly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,Receives audio from Pi or laptop headphone output,SJ1-3533NG,CP1-3533NG-ND,J8,1.69,Previous catalog check
Two-position power terminal block,2,0.58,DigiKey,https://www.digikey.com/en/products/detail/on-shore-technolo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,12V input and amplifier supply; 5.08mm pitch; manufacturer 1.30mm drill pattern checked against existing pads,OSTTC022162,ED2609-ND,J3 J4,1.16,USD catalog listing and manufacturer drawing reviewed 2026-10-22
USB resettable fuse,1,0.68,DigiKey,https://www.digikey.com/en/products/detail/littelfuse-inc/12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,USB supply overcurrent protection; 0.5A hold,1206L050/15YR,F3733CT-ND,F1,0.68,Previous catalog check
MINI blade fuse holder,1,1.31,DigiKey,https://www.digikey.com/en/products/detail/keystone-electron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,Holds amplifier supply fuse,3568,36-3568-ND,F2,1.31,Previous catalog check
2A MINI blade fuse,1,0.39,DigiKey,https://www.digikey.com/en/products/detail/littelfuse-inc/02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,Removable amplifier supply fuse,0297002.WXNV,F986-ND,F2 insert,0.39,Previous catalog check
Reverse-polarity diode,1,0.71,DigiKey,https://www.digikey.com/en/products/detail/taiwan-semiconduc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,Blocks reverse-polarity 12V input; DO-201AD,1N5822,1801-1N5822CT-ND,D1,0.71,Previous catalog check
Volume potentiometer,1,1.23,DigiKey,https://www.digikey.com/en/products/detail/bourns-inc/PTV09A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,10k audio volume control with 20mm shaft,PTV09A-2020F-A103,PTV09A-2020F-A103-ND,RV1,1.23,Previous catalog check
Audio source selector,1,0.80,DigiKey,https://www.digikey.com/en/products/detail/c-k/OS102011MS2QN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,Select AUX for this build; second source reserved for future DAC,OS102011MS2QN1,CKN9565-ND,SW3,0.80,Previous catalog check
RESET and BOOT buttons,2,0.35,DigiKey,https://www.digikey.com/en/products/detail/aratas-america-ll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,Manual reset and programming-mode controls,B3F-1000,SW400-ND,SW1 SW2,0.70,Previous catalog check
10uF ceramic capacitor,2,0.25,DigiKey,https://www.digikey.com/en/products/detail/samsung-electro-m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,Supply decoupling; 1206 X5R 25V,CL31A106KAHNFNE,1276-3038-1-ND,C1 C5,0.50,Previous catalog check
100nF ceramic capacitor,4,0.14,DigiKey,https://www.digikey.com/en/products/detail/samsung-electro-m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,Local supply bypass; 1206 X7R 50V,CL31B104KBCNNNC,1276-1017-1-ND,C2 C7 C9 C10,0.56,Previous catalog check
1uF ceramic capacitor,2,0.24,DigiKey,https://www.digikey.com/en/products/detail/samsung-electro-m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,Timing and supply bypass; 1206 X7R 50V,CL31B105KBHSNNE,1276-3093-1-ND,C3 C4,0.48,Previous catalog check
470uF electrolytic capacitor,1,1.06,DigiKey,https://www.digikey.com/en/products/detail/panasonic-industr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,Amplifier supply reservoir; 25V; 10mm body and 5mm pitch,EEU-FR1E471,P14419-ND,C6,1.06,Previous catalog check
2.2uF audio coupling capacitor,1,0.21,DigiKey,https://www.digikey.com/en/products/detail/samsung-electro-m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,Blocks DC in analog audio; nonpolar 1206 X7R 25V,CL31B225KAHNNNE,1276-1072-1-ND,C8,0.21,Previous catalog check
10k resistor,4,0.11,DigiKey,https://www.digikey.com/en/products/detail/yageo/RC1206FR-07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,Pull-ups and signal dividers; 1206 1% 0.25W,RC1206FR-0710KL,311-10.0KFRCT-ND,R1 R2 R13 R17,0.44,Previous catalog check
5.1k resistor,2,0.10,DigiKey,https://www.digikey.com/en/products/detail/yageo/RC1206FR-07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,USB-C CC pull-downs; 1206 1% 0.25W,RC1206FR-075K1L,311-5.10KFRCT-ND,R3 R4,0.20,Previous catalog check
22 ohm resistor,2,0.11,DigiKey,https://www.digikey.com/en/products/detail/yageo/RC1206FR-07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,USB series resistors; 1206 1% 0.25W,RC1206FR-0722RL,311-22.0FRCT-ND,R5 R6,0.22,Previous catalog check
4.7k resistor,6,0.10,DigiKey,https://www.digikey.com/en/products/detail/yageo/RC1206FR-07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,Audio mixing and I2C pull-ups; 1206 1% 0.25W,RC1206FR-074K7L,311-4.70KFRCT-ND,R9 R10 R11 R12 R18 R19,0.60,Previous catalog check
18k resistor,1,0.10,DigiKey,https://www.digikey.com/en/products/detail/yageo/RC1206FR-07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,Ultrasonic ECHO divider; 1206 1% 0.25W,RC1206FR-0718KL,311-18.0KFRCT-ND,R14,0.10,Previous catalog check
100k resistor,1,0.10,DigiKey,https://www.digikey.com/en/products/detail/yageo/RC1206FR-07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,Microphone data pull-down; 1206 1% 0.25W,RC1206FR-07100KL,311-100KFRCT-ND,R15,0.10,Previous catalog check
6.8k resistor,1,0.10,DigiKey,https://www.digikey.com/en/products/detail/yageo/RC1206FR-07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,Amplifier input attenuation; 1206 1% 0.25W,RC1206FR-076K8L,311-6.80KFRCT-ND,R16,0.10,Previous catalog check
40-pin breakaway header strip,1,1.23,DigiKey,https://www.digikey.com/en/products/detail/sullins-connector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,Cut into the seven carrier headers; 27 pins used,PRPC040SAAN-RC,S1011EC-40-ND,J5 J6 J7 J9 J10 J11 J12,1.23,Previous catalog check
I2S microphone breakout,1,6.95,DigiKey,https://www.digikey.com/en/products/detail/adafruit-industri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,SPH0645LM4H microphone wired to J9 by signal labels; configure firmware for this mic,3421,1528-1908-ND,External J9,6.95,USD catalog listing reviewed 2026-10-22
Mono amplifier module,1,6.99,ShillehTek,https://shillehtek.com/products/tpa3118-pbtl-single-digital-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,TPA3118 mono amplifier; use fused 12V input and separate speaker outputs,ST-HLHQRTMBQEIH,,External J4 J5,6.99,Manufacturer USD listing reviewed 2026-10-22
12V amplifier power supply,1,10.33,DigiKey,https://www.digikey.com/en/products/detail/tri-mag-llc/L6R30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,Enclosed 12V 2.5A US-wall adapter; center-positive 5.5x2.1mm plug,L6R30-120,364-1279-ND,External supply,10.33,USD catalog listing reviewed 2026-10-22
22 AWG insulated wire - 1m ten-conductor ribbon,1,4.25,DigiKey,https://www.digikey.com/en/products/detail/adafruit-industri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,Separate conductors for short regulator; amplifier and speaker wiring; mark each wire at both ends; avoid long I2S leads,6180,1528-6180-ND,REGULATOR_AND_SHORT_POWER_WIRING,4.25,USD catalog listing reviewed 2026-10-22
Female 2.1mm DC barrel to screw-terminal adapter,1,2.00,DigiKey,https://www.digikey.com/en/products/detail/adafruit-industri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,Connect enclosed center-positive 12V supply to J3 using short wire; verify polarity and terminal tightness,368,1528-1386-ND,12V_ADAPTER,2.00,USD catalog listing reviewed 2026-10-22
